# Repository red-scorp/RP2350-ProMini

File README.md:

```
 ######  ######   #####   #####  #######   ###         ######                #     #            
 #     # #     # #     # #     # #        #   #        #     # #####   ####  ##   ## # #    # # 
 #     # #     #       #       # #       #     #       #     # #    # #    # # # # # # ##   # # 
 ######  ######   #####   #####  ######  #     # ##### ######  #    # #    # #  #  # # # #  # # 
 #   #   #       #             #       # #     #       #       #####  #    # #     # # #  # # # 
 #    #  #       #       #     # #     #  #   #        #       #   #  #    # #     # # #   ## # 
 #     # #       #######  #####   #####    ###         #       #    #  ####  #     # # #    # # 
```

# RP2350-ProMini Project

The RP2350-ProMini project aims to create a replacement for the Arduino Pro Mini using the RP2350 MCU.

## RP2350-ProMini Board

The **RP2350-ProMini** board is a 4-layer board designed to accommodate the popular Raspberry Pi RP2350 MCU in the commonly used, but obsolete, Arduino Pro Mini footprint.

This project is a shoot-off from my earlier [RP2040-ProMini](https://github.com/red-scorp/RP2040-ProMini) project, which was designed to accommodate the Raspberry Pi RP2040 MCU in the same footprint.

Preview:

You can view the [Schematics in PDF format](doc/RP2350-ProMini.pdf) for detailed information.

STEP 3D files are available [with pins](doc/RP2350-ProMini-with-pins.step) and [without pins](doc/RP2350-ProMini-board.step).

Features:

- Arduino Pro Mini compatible pinout
- Partially compatible with Arduino Nano RP2040 Connect pinout
- Detachable USB and JTAG extension board with RESET button
- Dual-core Cortex-M33 Raspberry Pi RP2350
- Small footprint suitable for DIY projects
- 21 GPIO pins, including 4 analog inputs
- USB data pins on the side connector
- SWD debugging pins on the side connector
- Buck-Boost converter based 3.3V power supply with input range of 2.5V-12V
- Supports both SOIC and WSON 16MB flash packages
- Flat back side enables use as a sub-assembly
- Two cut points to reduce power consumption of unused components

CAM files, as well as the BOM and CPL files for JLCPCB, are available.

### Board Pinout

Following pinout is used for the board:

| Board Pin | RP2040 Pin | Function | Notes |
| --------- | ---------- | -------- | ----- |
| D0        | GPIO1      | UART0 TX |       |
| D1        | GPIO0      | UART0 RX |       |
| D2        | GPIO25     |          |       |
| D3        | GPIO15     |          |       |
| D4        | GPIO16     |          |       |
| D5        | GPIO17     |          |       |
| D6        | GPIO18     |          |       |
| D7        | GPIO19     |          |       |
| D8        | GPIO20     |          |       |
| D9        | GPIO21     |          |       |
| D10       | GPIO5      | SS       |       |
| D11       | GPIO7      | MOSI     |       |
| D12       | GPIO4      | MISO     |       |
| D13       | GPIO6      | SCK      | LED   |
| D14 A0    | GPIO26     |          |       |
| D15 A1    | GPIO27     |          |       |
| D16 A2    | GPIO28     |          |       |
| D17 A3    | GPIO29     |          |       |
| D18       | GPIO12     | SDA      |       |
| D19       | GPIO13     | SCL      |       |
| D20       | GPIO22     |          |       |
| D21       | GPIO23     |          |       |

### Cut Points

There are two cut points on the board to reduce power consumption of unused components.

| Cut Point | Function | Notes |
| --------- | -------- | ----- |
| CUT_VIN   | Separates VIN-to-3V3 power supply with power LED from the rest of the board | This cut point is useful if you want to power the board from 3V3 pin instead of VIN pin. |
| CUT_LED   | Separates LED on pin D13 from the rest of the board | This cut point is useful if you want to reduce power consumption of the board. |

## Version History

### v1.0b1 - xx.xx.2024

Initial release for testing purposes.

## Links

- [Raspberry Pi RP2350 information page](https://www.raspberrypi.com/documentation/microcontrollers/silicon.html#rp2350).
- [Arduino Pro Mini information page](https://docs.arduino.cc/retired/boards/arduino-pro-mini).
- [Arduino Nano RP2040 Connect page](https://docs.arduino.cc/hardware/nano-rp2040-connect).
- [Arduino SDK for RP2040/RP2350 board](https://github.com/earlephilhower/arduino-pico).

## How to Help

Your contributions as code, resources, or finances are welcome! Please contact me directly via email at andriy.golovnya@gmail.com or through my [GitHub profile](https://github.com/red-scorp).

If you'd like to make a financial contribution, you can donate via [PayPal](http://paypal.me/redscorp) or [Ko-Fi](http://ko-fi.com/redscorp). Your support is greatly appreciated.

Thanks in advance!

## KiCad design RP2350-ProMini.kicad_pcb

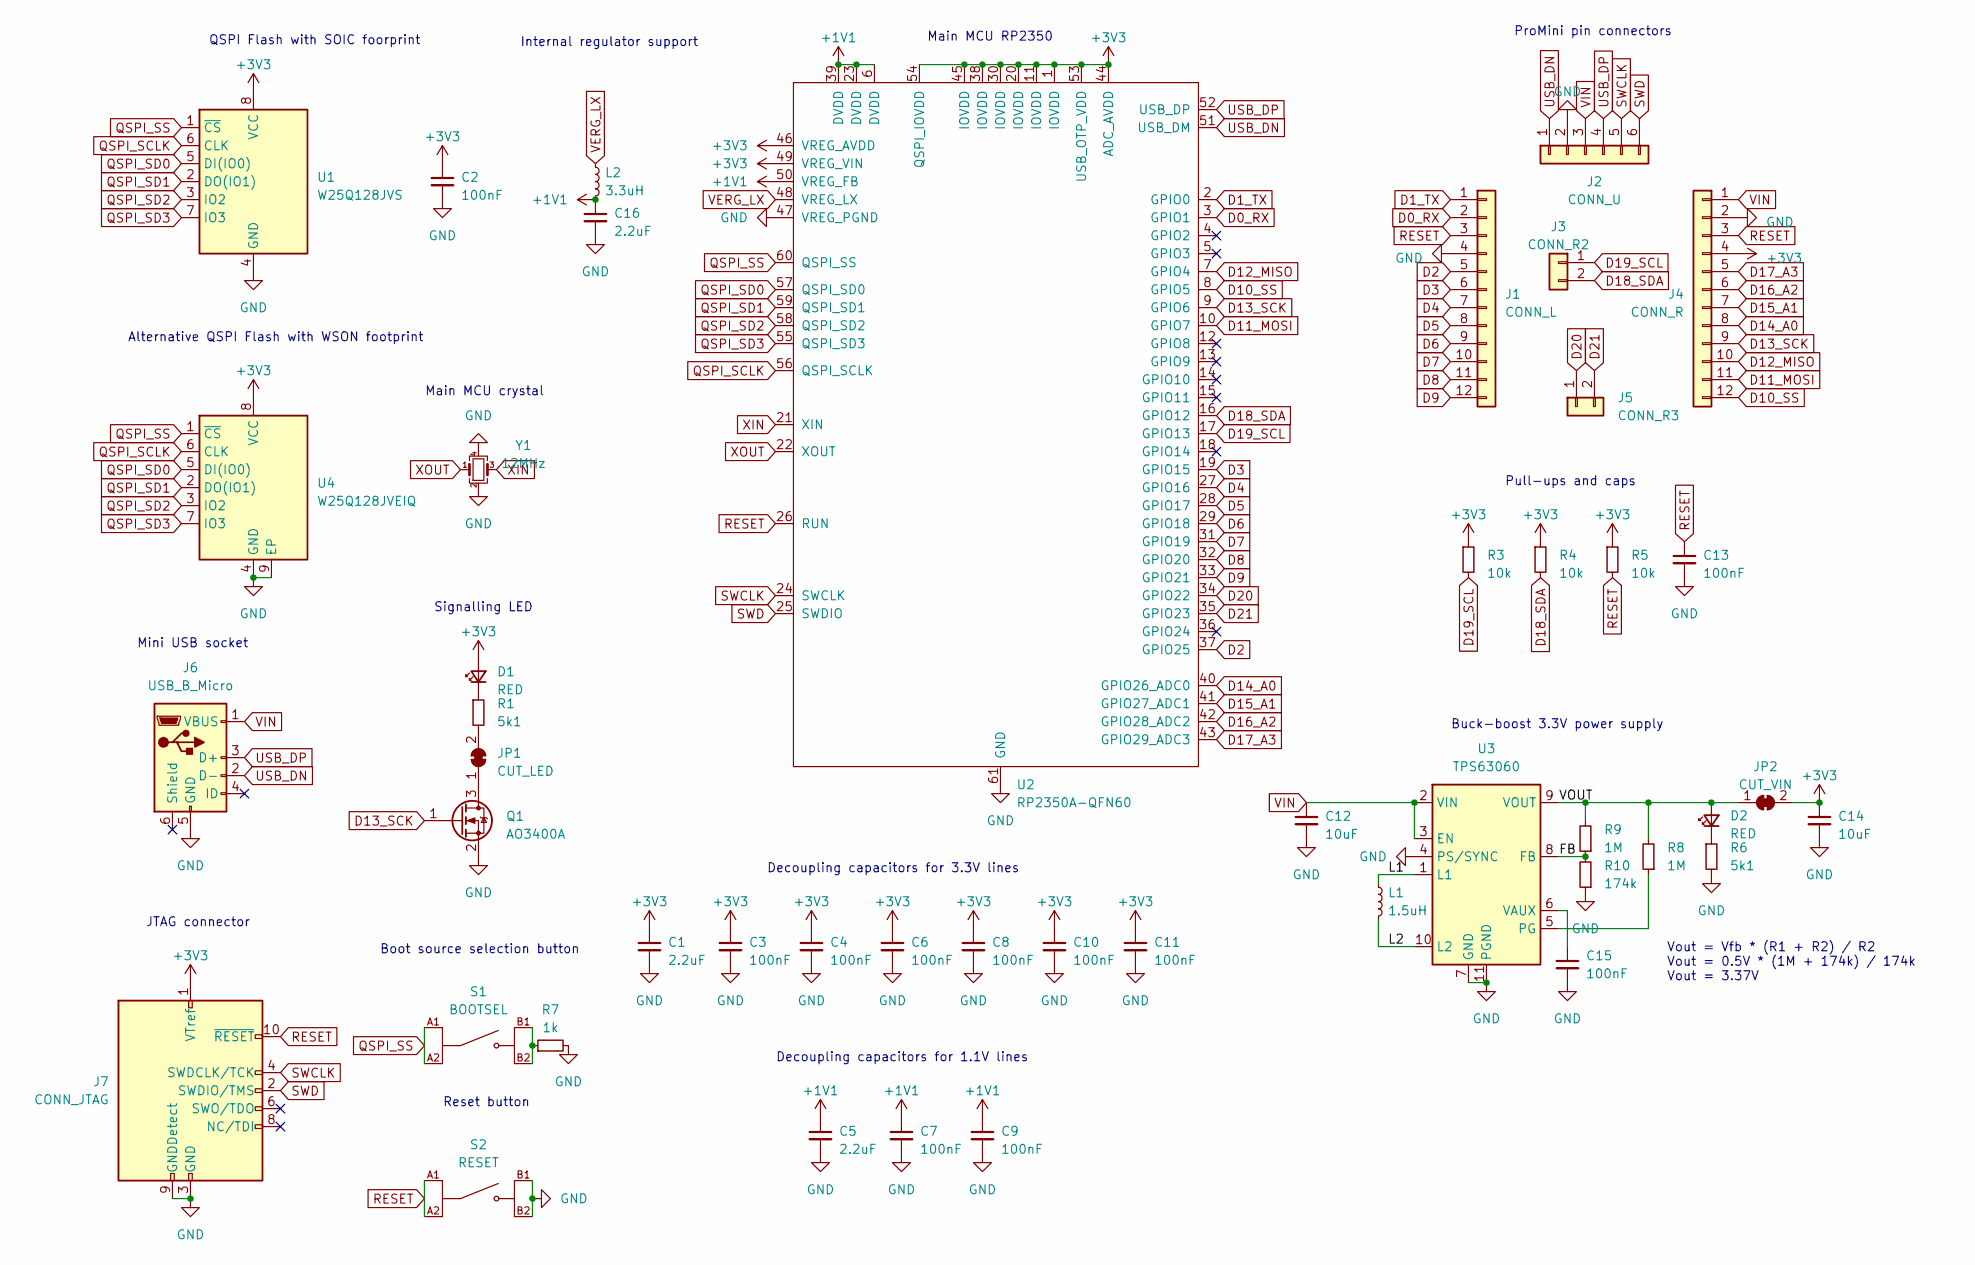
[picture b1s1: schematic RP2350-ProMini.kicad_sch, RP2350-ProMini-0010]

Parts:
C1, C5, C16: 2.2uF; C_0402_1005Metric
C2, C3, C4, C6, C7, C8, C9, C10, C11, C13, C15: 100nF; C_0402_1005Metric
C12, C14: 10uF; C_0805_2012Metric
D1, D2: RED; LED_0603_1608Metric
J1: CONN_L; PinHeader_1x12_P2.54mm_Vertical
J2: CONN_U; PinHeader_1x06_P2.54mm_Vertical
J3: CONN_R2; PinHeader_1x02_P2.54mm_Vertical
J4: CONN_R; PinHeader_1x12_P2.54mm_Vertical
J5: CONN_R3; PinHeader_1x02_P2.54mm_Vertical
J6: USB_B_Micro; USB_Micro-B_Molex_47346-0001
J7: CONN_JTAG; PinHeader_2x05_P1.27mm_Vertical_SMD
JP1: CUT_LED; SolderJumper-2_P1.3mm_Bridged_RoundedPad1.0x1.5mm
JP2: CUT_VIN; SolderJumper-2_P1.3mm_Bridged_RoundedPad1.0x1.5mm
L1: 1.5uH; L_Murata_DFE201610P
L2: 3.3uH; L_0603_1608Metric
Q1: AO3400A; SOT-23
R1, R6: 5k1; R_0402_1005Metric
R3, R4, R5: 10k; R_0402_1005Metric
R7: 1k; R_0402_1005Metric
R8, R9: 1M; R_0402_1005Metric
R10: 174k; R_0402_1005Metric
S1: BOOTSEL; SW_EVPBB0AAB000; DIGI-KEY_PART_NUMBER P19888CT-ND
S2: RESET; SW_EVPBB0AAB000; DIGI-KEY_PART_NUMBER P19888CT-ND
U1: W25Q128JVS; SOIC-8_5.23x5.23mm_P1.27mm
U2: RP2350A-QFN60; RP2350A_QFN-60_EP_7.75x7.75_Pitch0.4mm
U3: TPS63060; Texas_S-PWSON-N10_ThermalVias
U4: W25Q128JVEIQ; WSON-8-1EP_6x5mm_P1.27mm_EP3.4x4.3mm
Y1: 12MHz; Crystal_SMD_3225-4Pin_3.2x2.5mm

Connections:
+1V1: C5.1, C7.1, C9.1, C16.1, L2.2, U2.6 (DVDD), U2.23 (DVDD), U2.39 (DVDD), U2.50 (VREG_FB)
+3V3: C1.1, C2.1, C3.1, C4.1, C6.1, C8.1, C10.1, C11.1, C14.1, D1.2 (A), J4.4, J7.1 (VTref), JP2.2 (B), R3.1, R4.1, R5.1, U1.8 (VCC), U2.1 (IOVDD), U2.11 (IOVDD), U2.20 (IOVDD), U2.30 (IOVDD), U2.38 (IOVDD), U2.44 (ADC_AVDD), U2.45 (IOVDD), U2.46 (VREG_AVDD), U2.49 (VREG_VIN), U2.53 (USB_OTP_VDD), U2.54 (QSPI_IOVDD), U4.8 (VCC)
/FB: R9.1, R10.2, U3.8 (FB)
/L1: L1.1, U3.1 (L1)
/L2: L1.2, U3.10 (L2)
/VOUT: D2.2 (A), JP2.1 (A), R8.2, R9.2, U3.9 (VOUT)
D0_RX: J1.2, U2.3 (GPIO1)
D1_TX: J1.1, U2.2 (GPIO0)
D2: J1.5, U2.37 (GPIO25)
D3: J1.6, U2.19 (GPIO15)
D4: J1.7, U2.27 (GPIO16)
D5: J1.8, U2.28 (GPIO17)
D6: J1.9, U2.29 (GPIO18)
D7: J1.10, U2.31 (GPIO19)
D8: J1.11, U2.32 (GPIO20)
D9: J1.12, U2.33 (GPIO21)
D10_SS: J4.12, U2.8 (GPIO5)
D11_MOSI: J4.11, U2.10 (GPIO7)
D12_MISO: J4.10, U2.7 (GPIO4)
D13_SCK: J4.9, Q1.1 (G), U2.9 (GPIO6)
D14_A0: J4.8, U2.40 (GPIO26_ADC0)
D15_A1: J4.7, U2.41 (GPIO27_ADC1)
D16_A2: J4.6, U2.42 (GPIO28_ADC2)
D17_A3: J4.5, U2.43 (GPIO29_ADC3)
D18_SDA: J3.2, R4.2, U2.16 (GPIO12)
D19_SCL: J3.1, R3.2, U2.17 (GPIO13)
D20: J5.1, U2.34 (GPIO22)
D21: J5.2, U2.35 (GPIO23)
GND: C1.2, C2.2, C3.2, C4.2, C5.2, C6.2, C7.2, C8.2, C9.2, C10.2, C11.2, C12.2, C13.2, C14.2, C15.2, C16.2, J1.4, J2.2, J4.2, J6.5 (GND), J7.3 (GND), J7.5 (GND), J7.9 (GNDDetect), Q1.2 (S), R6.2, R7.2, R10.1, S2.B1, S2.B2, U1.4 (GND), U2.47 (VREG_PGND), U2.61 (GND), U3.4 (PS/SYNC), U3.7 (GND), U3.11 (PGND), U4.4 (GND), U4.9 (EP), Y1.2, Y1.4
unnamed: D1.1 (K), R1.1
unnamed: D2.1 (K), R6.1
unnamed: JP1.1 (A), Q1.3 (D)
unnamed: JP1.2 (B), R1.2
unnamed: R7.1, S1.B1, S1.B2
unnamed: R8.1, U3.5 (PG)
unnamed: C15.1, U3.6 (VAUX)
QSPI_SCLK: U1.6 (CLK), U2.56 (QSPI_SCLK), U4.6 (CLK)
QSPI_SD0: U1.5 (DI(IO0)), U2.57 (QSPI_SD0), U4.5 (DI(IO0))
QSPI_SD1: U1.2 (DO(IO1)), U2.59 (QSPI_SD1), U4.2 (DO(IO1))
QSPI_SD2: U1.3 (IO2), U2.58 (QSPI_SD2), U4.3 (IO2)
QSPI_SD3: U1.7 (IO3), U2.55 (QSPI_SD3), U4.7 (IO3)
QSPI_SS: S1.A1, S1.A2, U1.1 (~CS), U2.60 (QSPI_SS), U4.1 (~CS)
RESET: C13.1, J1.3, J4.3, J7.10 (~RESET), R5.2, S2.A1, S2.A2, U2.26 (RUN)
SWCLK: J2.5, J7.4 (SWDCLK/TCK), U2.24 (SWCLK)
SWD: J2.6, J7.2 (SWDIO/TMS), U2.25 (SWDIO)
USB_DN: J2.1, J6.2 (D-), U2.51 (USB_DM)
USB_DP: J2.4, J6.3 (D+), U2.52 (USB_DP)
VERG_LX: L2.1, U2.48 (VREG_LX)
VIN: C12.1, J2.3, J4.1, J6.1 (VBUS), U3.2 (VIN), U3.3 (EN)
XIN: U2.21 (XIN), Y1.3
XOUT: U2.22 (XOUT), Y1.1

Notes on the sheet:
Alternative QSPI Flash with WSON footprint
ProMini pin connectors
Main MCU RP2350
Decoupling capacitors for 3.3V lines
Vout = Vfb * (R1 + R2) / R2 Vout = 0.5V * (1M + 174k) / 174k Vout = 3.37V
Main MCU crystal
Decoupling capacitors for 1.1V lines
Pull-ups and caps
Signalling LED
JTAG connector
Reset button
Mini USB socket
Boot source selection button
Buck-boost 3.3V power supply
Internal regulator support
QSPI Flash with SOIC foorprint

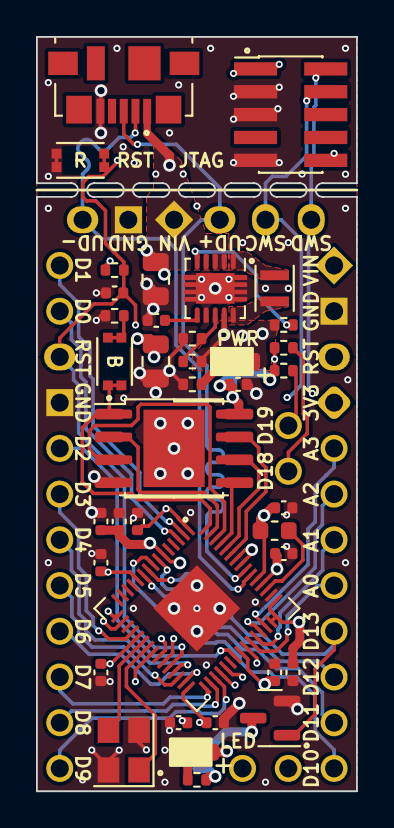
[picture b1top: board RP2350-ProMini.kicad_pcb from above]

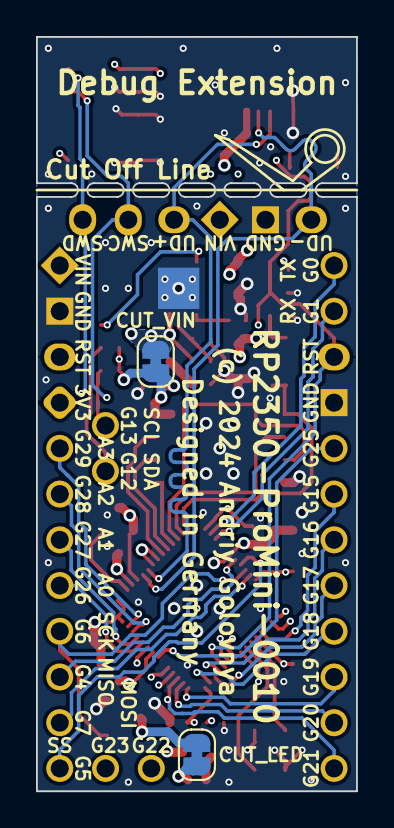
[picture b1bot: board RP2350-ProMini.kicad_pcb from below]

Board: 4 copper layers, 17.8 x 41.9 mm, 46 parts (7 on the bottom side), 51 nets.

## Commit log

2024-08-31 Initial design based on RP2040-ProMini
2024-08-31 Use wrl instead of step 3d model for RP2350
2024-09-01 Added some routing
2024-09-01 Added README.md
2024-09-03 Moved staff around.
2024-09-06 Improved USB data lines
2024-09-22 Generated CAM file
2024-09-22 Generated PDF schematics
2024-09-22 Generated PNG preview
2024-09-22 Generated STEP 3D model
2024-09-22 Added generic JLCPCB BOM
2024-09-22 Added generic JLCPCB CPL
2024-10-08 Fixed USB tracers length.
2024-10-08 Generated CAM files

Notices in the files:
RP2350-ProMini.kicad_pcb:
(c) 2024 Andriy Golovnya
